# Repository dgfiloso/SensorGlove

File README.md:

# SensorGlove

## Introducción
SensorGlove es un proyecto realizado por 6 alumnos de la Escuela Técnica Superior de Ingenieros de Telecomunicación, Universidad Politécnica de Madrid, para la asignatura Electrónica de Consumo. Este proyecto consiste en realizar el desarrollo completo de un producto para llevarlo al mercado, siguiendo etapas como la realización de un prototipo, la búsqueda de proveedores y fabricantes, el diseño del producto final y la comercialización y difusión del producto.

## Producto
SensorGlove surge como una idea de reinventar el modelismo y conseguir una mayor inmersión del conductor en el dispositivo radiocontrol. Nuestro equipo ha desarrollado un guante autónomo capaz de detectar los movimientos de una mano y enviar los datos de manera inalámbrica. Una de las últimas tendencias tecnológicas y que cada vez se encuentra más presente en nuestro día a día es la realidad virtual, y creemos que nuestro producto es un complemento perfecto para esta tecnología del futuro.

Sin embargo, una de las ventajas de nuestro producto es que tiene una infinidad de aplicaciones, y aunque en este proyecto su propósito sea el modelismo, en un futuro queremos abrir el proyecto a nuevos sectores.

## Prototipo
El prototipo se encuentra dividido en dos partes claramente diferenciadas, el guante y el coche radiocontrol. Ambos partes se han desarrollado usando la placa de desarrollo Arduino Nano, con lo que hemos conseguido un rápido prototipado para ver si nuestro proyecto era viable y poder probar de una manera sencilla los diferentes módulos que usaremos en nuestro producto final.

El guante utiliza tres módulos principales:
+	MPU6050 : Acelerómetro-giróscopo de 6 ejes con el que medimos el ángulo con respecto al eje X y al eje Y.
+	Flex Sensor : Sensor desarrollado por Sparkfun. Se trata de una resistencia que varía su valor en función de cuanto se dobla.
+	NRF24L01 : Transceptor radio que funciona a 2,4 GHz con el que transmitimos los datos.

El coche utiliza dos módulos:
+	NRF24L01 : Transceptor radio que funciona a 2,4 GHz con el recibir los datos del guante.
+	Etapa de potencia: Utilizada para mover los motores del coche radiocontrol.

## Difusión
Para dar a conocer nuestro producto contamos con la página web oficial del proyecto:
+	https://sensorglove.wixsite.com/sensorglove

Además contamos con distintas redes sociales:
+	[Facebook](https://www.facebook.com/Sensor-Glove-428774670806512/)
+	[Twitter](https://twitter.com/sensorglove)
+	[YouTube](https://www.youtube.com/channel/UCL0-cJEzkYREWF3CBP17AOg)

## Equipo
+ Diego Poderoso
+ Laura del Rio
+ Ana Pereira
+ Rodrigo Morrás
+ Daniel Fortún 
+ David González Filoso

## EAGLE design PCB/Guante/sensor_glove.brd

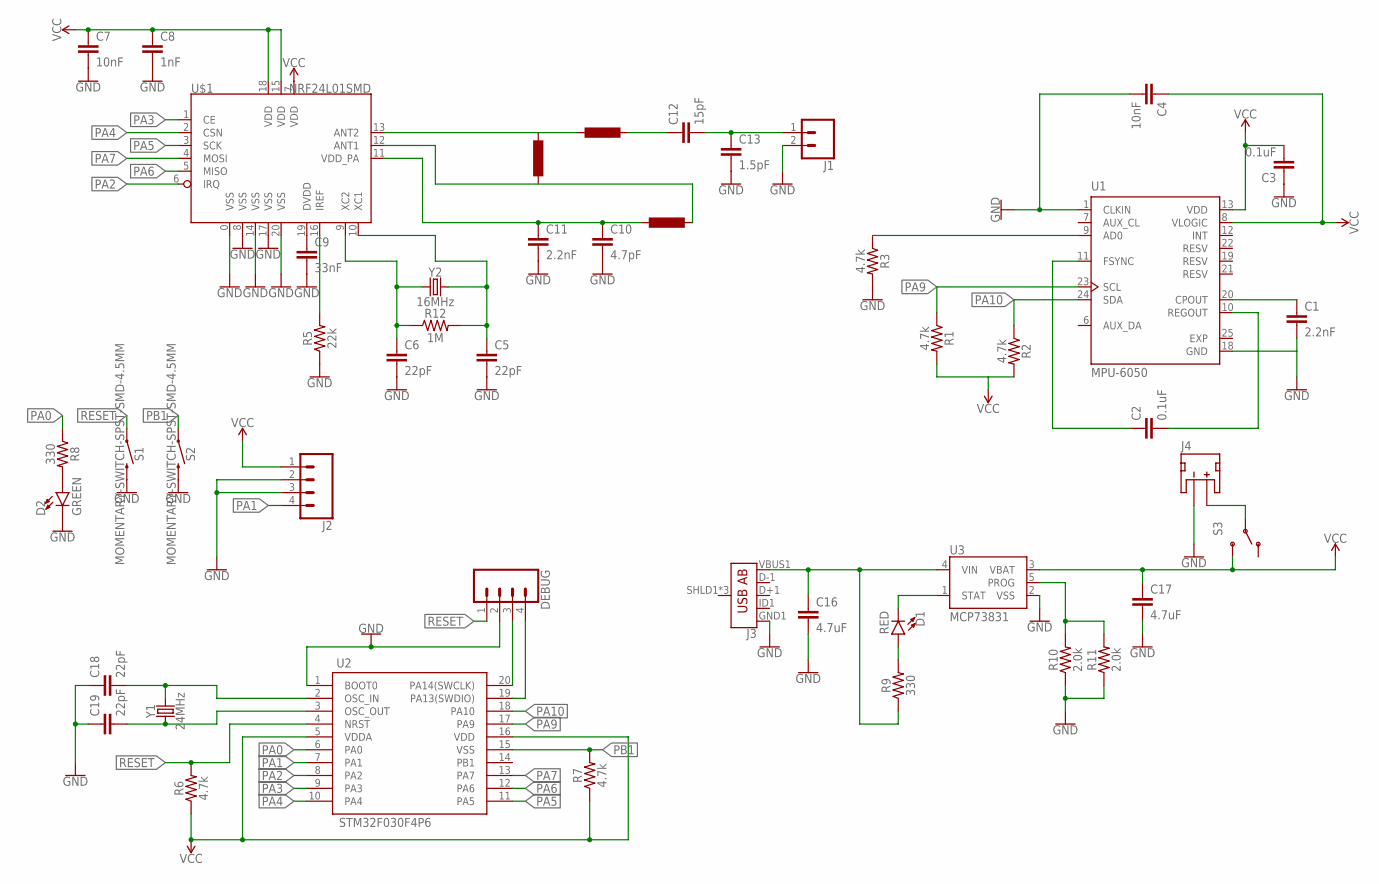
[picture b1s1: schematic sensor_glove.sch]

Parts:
C1, C11: 2.2nF; 0603
C2, C3: 0.1uF; 0402
C4, C7: 10nF; 0603
C5, C6, C18, C19: 22pF; 0603
C8: 1nF; 0603
C9: 33nF; 0603
C10: 4.7pF; 0603
C12: 15pF; 0402
C13: 1.5pF; 0603
C16, C17: 4.7uF; 0603
D1: RED; LED-0603
D2: GREEN; LED-0603
DEBUG: CONN_04; 1X04
J1: CONN_02; 1X02
J2: CONN_04; 1X04
J3: USB_AB_SMT; USB-AB-MICRO-SMD
J4: JST_2MM_MALE; JST-2-SMD
R1, R2, R3, R6, R7: 4.7k; 0603
R5: 22k; 0603
R8, R9: 330; 0603
R10, R11: 2.0k; 0603
R12: 1M; 0603
S1, S2: MOMENTARY-SWITCH-SPST-SMD-4.5MM; TACTILE_SWITCH_SMD_4.5MM
S3: SWITCH-SPDTSMD; SWITCH_SPDT_SMD
U1: MPU-6050; QFN50P400X400X95-25N
U2: STM32F030F4P6; TSSOP20-STM32
U3: MCP73831; SOT23-5
U$1: NRF24L01SMD; QFN20-4X4MM
Y1: 24MHz; CRYSTAL-SMD-5X3.2-4PAD
Y2: 16MHz; HC49US

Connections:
CON: J4.2 (+), S3.2
EXP: U1.25 (EXP)
FSYNC: C2.1, U1.11 (FSYNC)
GND: C3.1, C4.2, C5.2, C6.2, C7.2, C8.2, C9.2, C10.2, C11.2, C13.2, C16.2, C17.2, C18.1, C19.1, D2.C, DEBUG.2, J1.2, J2.2, J2.3, J3.GND1 (GND), J4.1 (-), R3.2, R5.1, S1.1 (2), S1.4 (2), S2.1 (2), S2.4 (2), U1.1 (CLKIN), U2.1 (BOOT0), U$1.0 (VSS), U$1.8 (VSS), U$1.14 (VSS), U$1.17 (VSS), U$1.20 (VSS)
unnamed: R3.1, U1.9 (AD0)
unnamed: C16.1, J3.VBUS1 (VBUS), R9.1, U3.4 (VIN)
unnamed: DEBUG.3, U2.20 (PA14(SWCLK))
unnamed: C6.1, R12.1, U$1.9 (XC2), Y2.1
unnamed: C1.1, U1.20 (CPOUT)
unnamed: C1.2, U1.18 (GND)
unnamed: C5.1, R12.2, U$1.10 (XC1), Y2.2
unnamed: C10.1, C11.1, U$1.11 (VDD_PA)
unnamed: C9.1, U$1.19 (DVDD)
unnamed: R5.2, U$1.16 (IREF)
unnamed: C12.2, C13.1, J1.1
unnamed: C18.2, U2.2 (OSC_IN), Y1.3 (2)
unnamed: C19.2, U2.3 (OSC_OUT), Y1.1
unnamed: DEBUG.4, U2.19 (PA13(SWDIO))
unnamed: D2.A, R8.2
unnamed: D1.C, U3.1 (STAT)
unnamed: D1.A, R9.2
unnamed: R10.2, R11.2, U3.5 (PROG)
unnamed: R10.1, R11.1
PA0: R8.1, U2.6 (PA0)
PA1: J2.4, U2.7 (PA1)
PA2: U2.8 (PA2), U$1.6 (IRQ)
PA3: U2.9 (PA3), U$1.1 (CE)
PA4: U2.10 (PA4), U$1.2 (CSN)
PA5: U2.11 (PA5), U$1.3 (SCK)
PA6: U2.12 (PA6), U$1.5 (MISO)
PA7: U2.13 (PA7), U$1.4 (MOSI)
PA9: R1.1, U1.23 (SCL), U2.17 (PA9)
PA10: R2.1, U1.24 (SDA), U2.18 (PA10)
PB1: R7.2, S2.2 (1), S2.3 (1), U2.15 (VSS)
REGOUT: C2.2, U1.10 (REGOUT)
RESET: DEBUG.1, R6.2, S1.2 (1), S1.3 (1), U2.4 (NRST)
VCC: C3.2, C4.1, C7.1, C8.1, C17.1, J2.1, R1.2, R2.2, R6.1, R7.1, S3.3 (S), U1.8 (VLOGIC), U1.13 (VDD), U2.5 (VDDA), U2.16 (VDD), U3.3 (VBAT), U$1.7 (VDD), U$1.15 (VDD), U$1.18 (VDD)

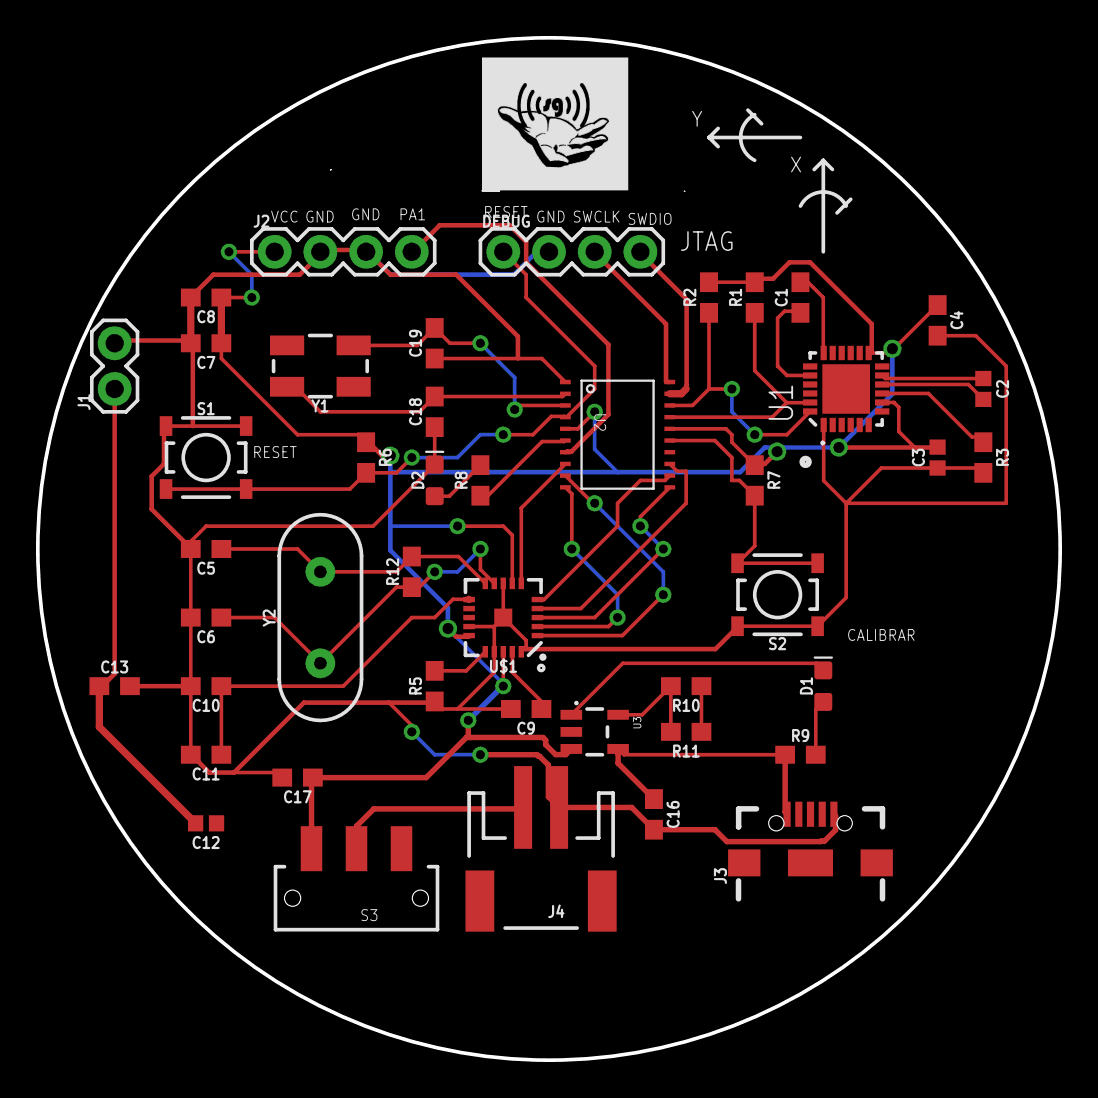
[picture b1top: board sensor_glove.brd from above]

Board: 2 copper layers, 56.8 x 56.8 mm, 44 parts (0 on the bottom side), 36 nets.

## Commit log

2017-04-06 Creado proyecto Se ha implementado la recepción de datos del MPU9250 aunque continua fallando
2017-04-07 Organización en carpetas para los dos módulos del proyecto
2017-04-07 Carpeta para el receptor
2017-04-19 Sensado Problemas con el I2C, error de bus ocupado.
2017-04-21 Por problemas con el hardware del SensorTag y de tiempo, hemos migrado el proyecto a una plataforma Arduino.
2017-04-21 Implementando funcionalidad del guante.
2017-04-22 Calibración y sensado conseguido
2017-04-22 Borrado fichero de Readme Texas
2017-05-03 Código implementado completamente, nos encontramos en periodo de pruebas.
2017-05-03 Pruebas realizadas, todo funcionando. Se ha comentado el calibrado y la impresión por puerto serie de trazas.
2017-05-04 Actualizado README.md
2017-05-04 Revisión README.md
2017-05-09 Cambiado valor resistivo del Flex Sensor con un ángulo de 90º
2017-05-09 Primera versión de la PCB del producto final
2017-05-10 Añadido interruptor en la PCB

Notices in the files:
parts and their libraries:
SparkFun-Capacitors: Licensing: Creative Commons ShareAlike 4.0 International - https://creativecommons.org/licenses/by-sa/4.0
